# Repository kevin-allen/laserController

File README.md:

# laserController

This repository describes our setup used to perform optogenetic stimulation in behavioral experiments. 

The laser pulses are controlled using a Python script and a TTL signal delivered from an Arduino Uno.

## Material needed

* Arduino Uno
* Arduino Shield (see Eagle files)
* USB cable
* Ethernet cable
* Ethernet socket for the Arduino shield
* Laser head ()
* Laser power ()
* ...

## Arduino shield

The Eagle files of the Arduino sheild are in the folder eagleFiles. You can use these files to generate Gerber files and order the shield from EuroCircuits.
The shield has one Ethernet cable that goes to the laser power box. There are 2 BNC sockets that can be used to send the TTL and power signal to the recording system. The signal will range from 0 to 5V so make sure that the hardware accepting these signals can cope with a 5V signal.

## Installation steps

Ethernet socket:
* pin 2: analog input, set power (0 to 5V defines the ratio of maximum power as defined using the manual poti)
* pin 3: pulse on/off (TTL)
* pin 4 & 5: connect together, apply HIGH for ON, apply LOW for OFF, don't apply any voltage there: key will turn on/off
* pin 6: ground

# Laser controller ROS

These *topics* are subscribed to by the Arduino connected to the Laser controller.

 *   `laser_enable`: bool enabled/disabled
 *   `laser_power`: byte 0-255 relative power of max power set on controller
 *   `laser_pulselen_on`: pulse length [ms] = 1/(2*frequency),  
       duty cycle on [ms] = laser_pulselen_on / (laser_pulselen_on + laser_pulselen_off)
 *   `laser_pulselen_off`: pulse off time [ms], set 0 for constant on

The former (`laser_controller__pulse50dutycycle.old`) sketch only had fixed 50% duty cycle and `laser_pulselen` as corresponding ros topic.

# Usage example
 You can
 - use the example file `python_ros_example/control_laser.py` and set the power, pulse_len and duty_cycle , or
 - use rostopic to publish , see description like in `sketches/laser_controller_ros/laser_controller_ros.ino`
     *   enable: `rostopic pub -1 /laser_enable std_msgs/Bool 1`
     *   set power: `rostopic pub -1 /laser_power std_msgs/UInt8 200`
     *   set pulse len on duration: `rostopic pub -1 /laser_pulselen_on std_msgs/UInt32 5`
     *   set pulse len off duration: `rostopic pub -1 /laser_pulselen_off std_msgs/UInt32 95`

# pulse length, frequency and duty cycle
- $t_\mathrm{on}$: pulse len on duration
- $t_\mathrm{off}$: pulse len off duration
- $T=t_\mathrm{on}+t_\mathrm{off}$: period duration
- $f=\frac{1}{T}$: frequency
- $d = \frac{t_\mathrm{on}}{T}$: duty cycle ( $0 < d \leq 1$ ), <sup><sub>The case `d=1` is treated individually and handled without timers.</sub></sup>

example ( [paper](https://pubmed.ncbi.nlm.nih.gov/35584671/) ):
"stimulation at 10 Hz with a 5 ms duration "
- $f=10\mathrm{Hz},\ T=100\mathrm{ms},\ t_\mathrm{on}=5\mathrm{ms},\ d=0.05$  (this example is acheived by above ros command)

Nota bene: The effective power (measured on average) will scale $\propto d$ as this is the raio of on duration.

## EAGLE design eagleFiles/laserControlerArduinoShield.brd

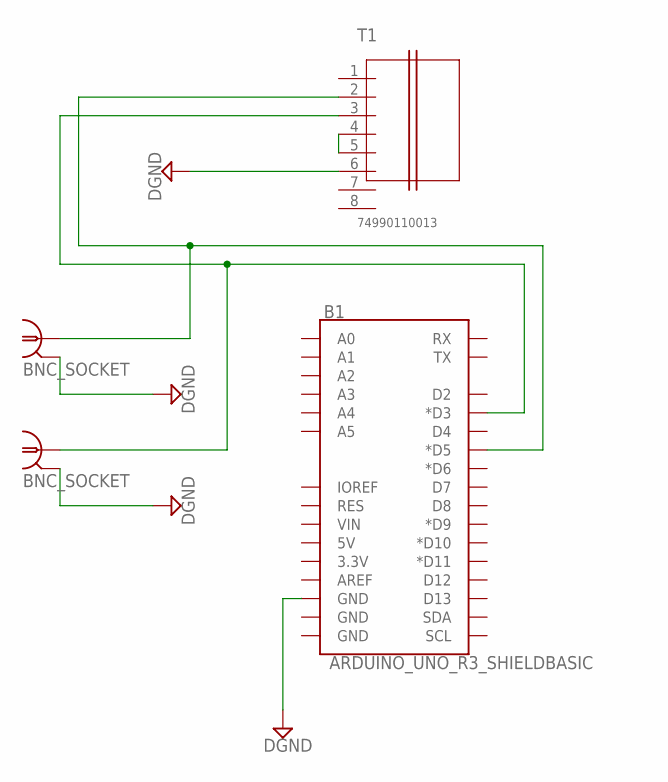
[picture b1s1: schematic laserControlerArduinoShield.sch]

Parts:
B1: ARDUINO_UNO_R3_SHIELDBASIC; UNO_R3_SHIELD
BNC_POWER: BNC_SOCKET
BNC_TTL: BNC_SOCKET
T1: 74990110013; 01LAN_RJ45_10/00_STD

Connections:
DGND: B1.GND@2 (GND), BNC_POWER.P$1 (2), BNC_POWER.P$2 (2), BNC_POWER.P$3 (2), BNC_POWER.P$4 (2), BNC_TTL.P$1 (2), BNC_TTL.P$2 (2), BNC_TTL.P$3 (2), BNC_TTL.P$4 (2), T1.6
unnamed: B1.D5 (*D5), BNC_TTL.P$SIGNAL (1), T1.2
unnamed: B1.D3 (*D3), BNC_POWER.P$SIGNAL (1), T1.3
unnamed: T1.4, T1.5

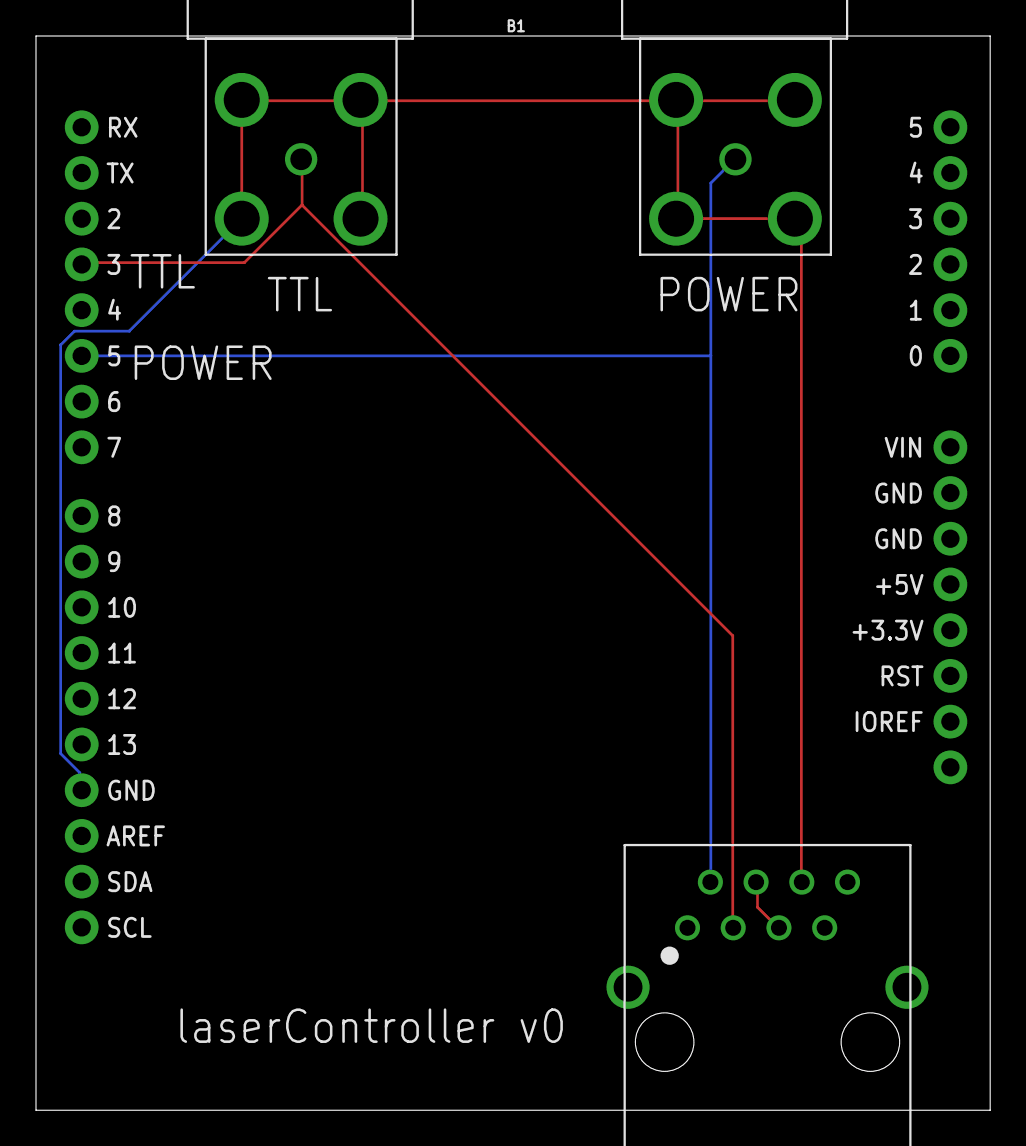
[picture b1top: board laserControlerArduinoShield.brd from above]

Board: 2 copper layers, 53.0 x 59.7 mm, 4 parts (0 on the bottom side), 4 nets.

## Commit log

2023-06-12 eagle sketch
2023-06-14 connect pins 4-5 in ethernet connector to turn the laser on
2023-06-16 add bnc connectors to arduino shield to sent ttl to recording system
2023-06-16 Arduino ros sketch, example python script, update documentation
2023-06-16 add AutoPI laser prog
2023-06-16 Readme
2023-06-23 openscad part to hold the beam splitter
2023-06-26 new actuator top with part to hold the optic fiber
2023-06-26 Add files via upload
    add the optic connector holder for the splitter
2023-06-28 Update README.md
    ros topics, background information (pulse duration, frequency, duty cycle, example paper)
2023-06-28 Update README.md
    typo
2023-06-28 Update README.md
    explanation on power measured on average

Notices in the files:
parts and their libraries:
SparkFun-Boards: Licensing: Creative Commons ShareAlike 4.0 International - https://creativecommons.org/licenses/by-sa/4.0
wurth_electronics_midcom_inc_v1-0: Copyright: Wurth Electronics Midcom, Inc.
